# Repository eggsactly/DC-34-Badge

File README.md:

# About
DC-34 Badge contains the KiCad 6 design files for the Cyber Professionals 
Enthusiast Club (CPEC) DEFCON 34 Badge. 

## Board Features
- 2.2" 320x240 display
- Wifi and Bluetooth LE equiped
- 3 Shitty Add On (SAO) 1.69bis ports equiped with I2C
- Gameboy equivalent buttons
- Rumble pack

## Project Structure
The structure of this repo is organized as such:

| Directory               | About                                                   |
|:------------------------|:--------------------------------------------------------|
| DC-34-Badge             | KiCad 6 Design files                                    |
| digikey-kicad-libraries | Symbol libraries and footprints downloaded from digikey |
| kicad-libraries         | git subtree containing expressif design files           |

## Running
To view schematics, please run KiCad 6.0.11 or later. Change directory into 
DC-34-Badge and run
```
kicad DC-34-Badge.kicad_pro
```

Please note: please run kicad from the same directory as the .kicad_pro file 
is stored because the fp-lib-table and sym-lib-table use relative paths 
so that this project is portable between computers.

# Associated Repos
Board firmware is developed in this repo: 
[https://github.com/wildcat86/DC34-Mech-Badge](https://github.com/wildcat86/DC34-Mech-Badge)

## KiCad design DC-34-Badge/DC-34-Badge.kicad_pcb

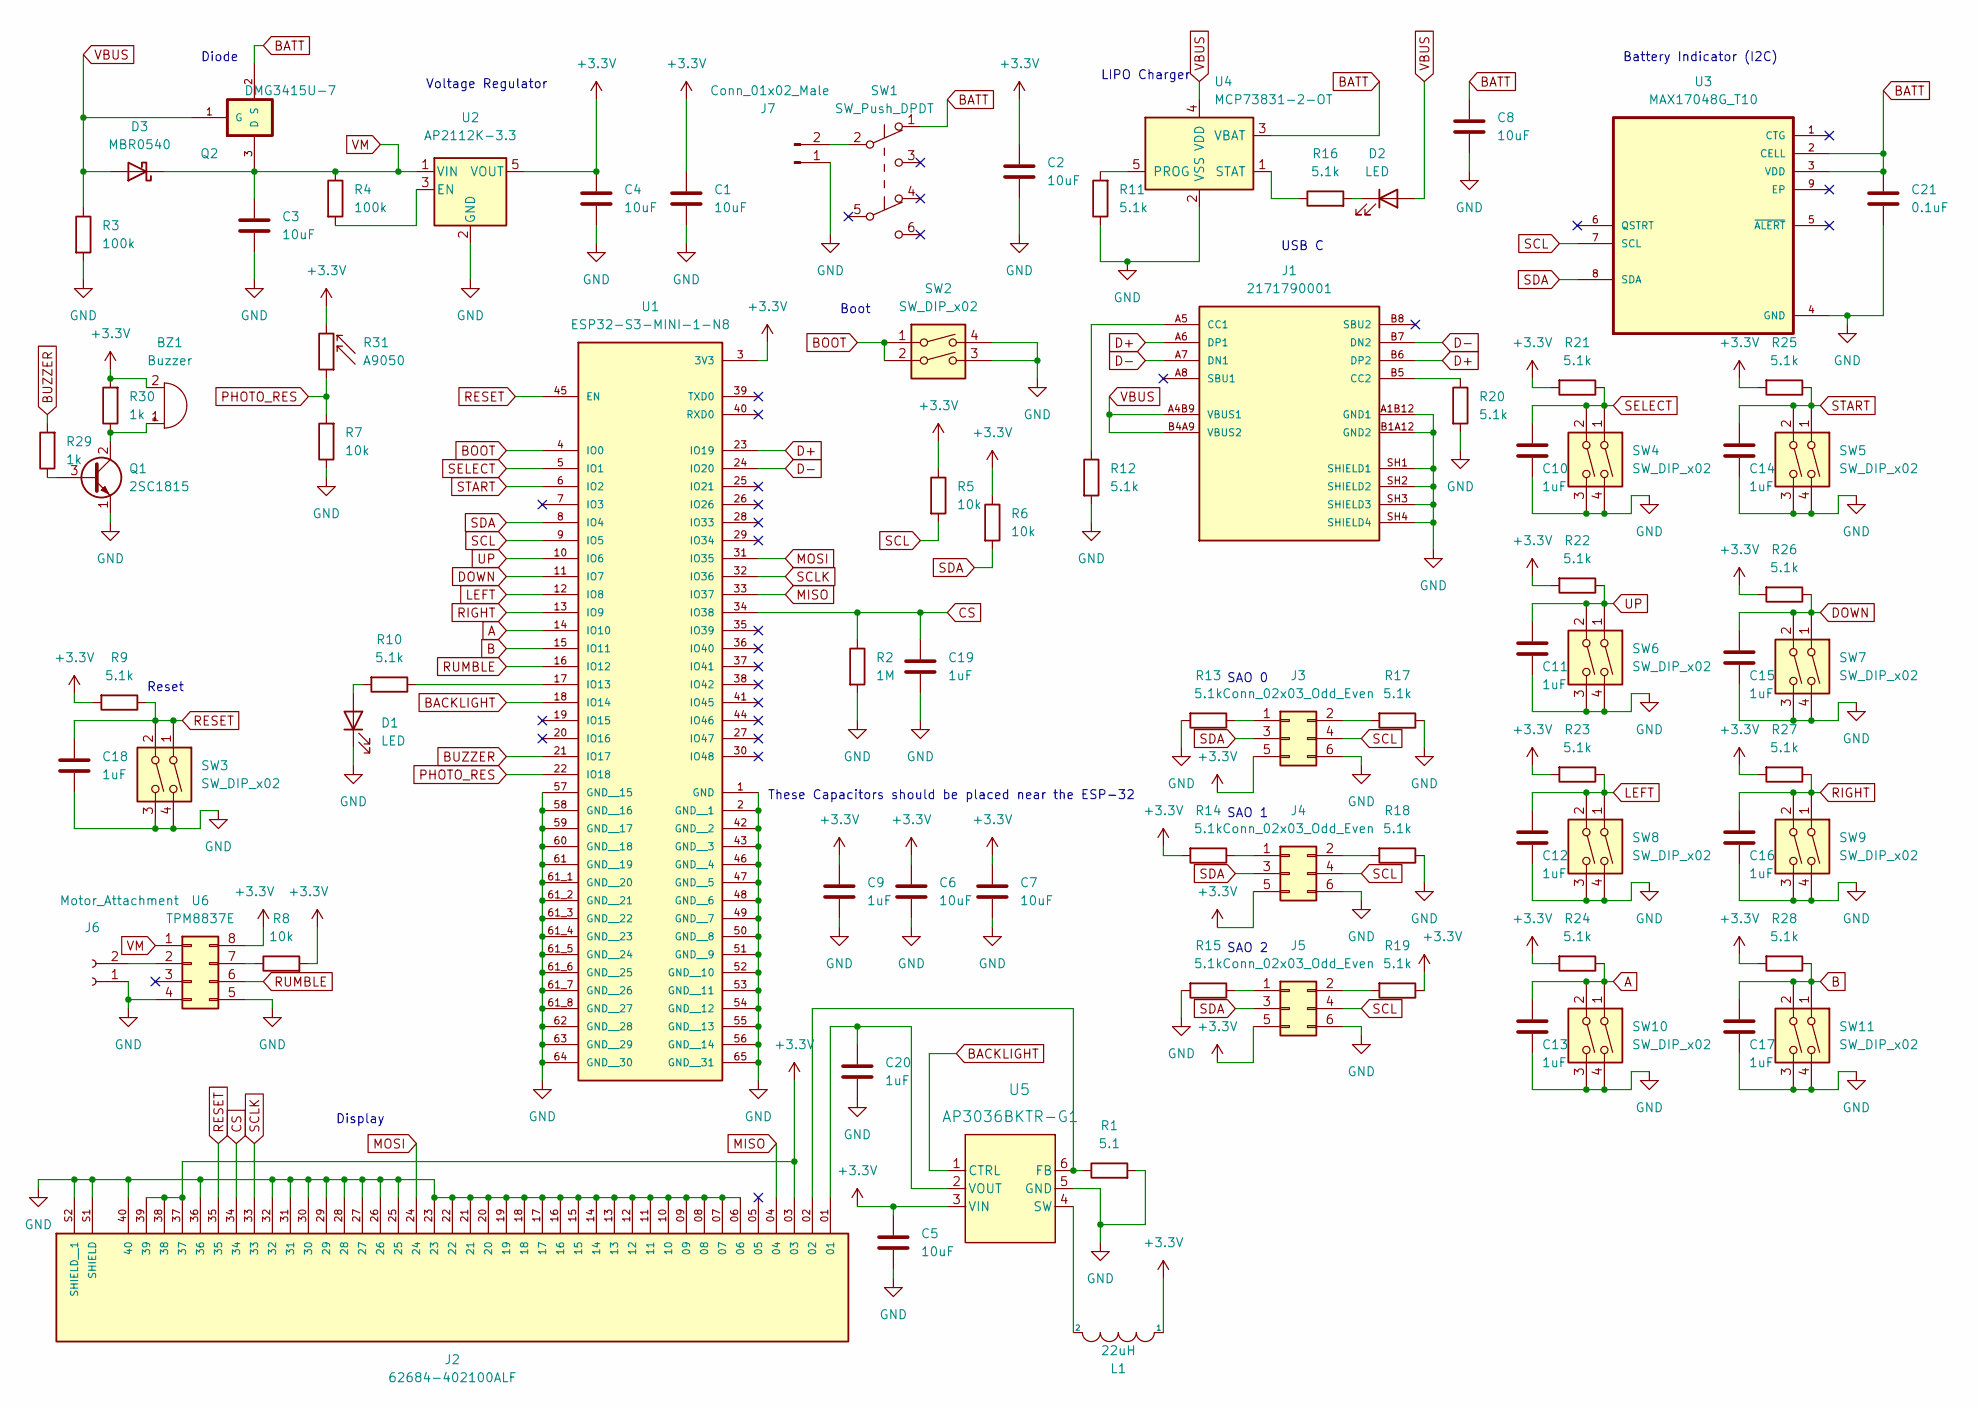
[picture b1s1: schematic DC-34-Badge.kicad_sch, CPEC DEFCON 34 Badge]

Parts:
BZ1: Buzzer; D_A-405_P5.08mm_Vertical_AnodeUp
C1, C2, C3, C4, C5, C6, C7, C8: 10uF; C_0402_1005Metric
C9, C10, C11, C12, C13, C14, C15, C16, C17, C18, C19, C20: 1uF; C_0402_1005Metric
C21: 0.1uF; C_0402_1005Metric
D1, D2: LED; LED_0201_0603Metric
D3: MBR0540; D_SOD-123
J1: 2171790001; MOLEX_2171790001; PARTREV A1
J2: 62684-402100ALF; AMPHENOL_62684-402100ALF; PARTREV AK
J3, J4, J5: Conn_02x03_Odd_Even; PinHeader_2x03_P2.54mm_Vertical
J6: Motor_Attachment; SolderWire-0.1sqmm_1x02_P3.6mm_D0.4mm_OD1mm
J7: Conn_01x02_Male; JST_XH_B2B-XH-AM_1x02_P2.50mm_Vertical
L1: 22uH; L_1210_3225Metric
Q1: 2SC1815; SOT-23
Q2: DMG3415U-7; SOT95P240X105-3N; MPN DMG3415U-7
R1: 5.1; R_0402_1005Metric
R2: 1M; R_0402_1005Metric
R3, R4: 100k; R_0402_1005Metric
R5, R6, R7, R8: 10k; R_0402_1005Metric
R9, R10, R11, R12, R13, R14, R15, R16, R17, R18, R19, R20, R21, R22, R23, R24, R25, R26, R27, R28: 5.1k; R_0402_1005Metric
R29, R30: 1k; R_0402_1005Metric
R31: A9050; R_LDR_5.0x4.1mm_P3mm_Vertical
SW1: SW_Push_DPDT; SW_CuK_JS202011CQN_DPDT_Straight
SW2, SW3, SW4, SW5, SW6, SW7, SW8, SW9, SW10, SW11: SW_DIP_x02; SW_PUSH_6mm
U1: ESP32-S3-MINI-1-N8; XCVR_ESP32-S3-MINI-1-N8; PARTREV v0.6
U2: AP2112K-3.3; SOT-23-5
U3: MAX17048G_T10; SON50P200X200X80-9N
U4: MCP73831-2-OT; SOT-23-5
U5: AP3036BKTR-G1; SOIC6_AP3036BKTR-G1_DIO
U6: TPM8837E; DFN-8-1EP_2x2mm_P0.5mm_EP0.8x1.6mm

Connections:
+3.3V: BZ1.2 (+), C1.1, C2.1, C4.1, C5.1, C6.1, C7.1, C9.1, J2.03, J2.37, J2.38, J2.39, J3.5, J4.5, J5.5, L1.1, R5.1, R6.1, R8.2, R9.2, R14.2, R19.1, R21.2, R22.2, R23.2, R24.2, R25.2, R26.2, R27.2, R28.2, R30.2, R31.2, U1.3 (3V3), U2.5 (VOUT), U5.3 (VIN), U6.8
A: C13.1, R24.1, SW10.1, SW10.2, U1.14 (IO10)
B: C17.1, R28.1, SW11.1, SW11.2, U1.15 (IO11)
BACKLIGHT: U1.18 (IO14), U5.1 (CTRL)
BATT: C8.1, C21.1, Q2.2 (S), SW1.1 (A), U3.2 (CELL), U3.3 (VDD), U4.3 (VBAT)
BOOT: SW2.1, SW2.2, U1.4 (IO0)
BUZZER: R29.2, U1.21 (IO17)
CS: C19.1, J2.34, R2.1, U1.34 (IO38)
D+: J1.A6 (DP1), J1.B6 (DP2), U1.23 (IO19)
D-: J1.A7 (DN1), J1.B7 (DN2), U1.24 (IO20)
DOWN: C15.1, R26.1, SW7.1, SW7.2, U1.11 (IO7)
GND: C1.2, C2.2, C3.2, C4.2, C5.2, C6.2, C7.2, C8.2, C9.2, C10.2, C11.2, C12.2, C13.2, C14.2, C15.2, C16.2, C17.2, C18.2, C19.2, C20.2, C21.2, D1.1 (K), J1.A1B12 (GND1), J1.B1A12 (GND2), J1.SH1 (SHIELD1), J1.SH2 (SHIELD2), J1.SH3 (SHIELD3), J1.SH4 (SHIELD4), J2.06, J2.07, J2.08, J2.09, J2.10, J2.11, J2.12, J2.13, J2.14, J2.15, J2.16, J2.17, J2.18, J2.19, J2.20, J2.21, J2.22, J2.23, J2.25, J2.26, J2.27, J2.28, J2.29, J2.30, J2.31, J2.32, J2.36, J2.40, J2.S1 (SHIELD), J2.S2 (SHIELD__1), J3.6, J4.6, J5.6, J6.1, J7.1, Q1.1 (E), R1.2, R2.2, R3.2, R7.1, R11.1, R12.2, R13.2, R15.2, R17.1, R18.1, R20.2, SW2.3, SW2.4, SW3.3, SW3.4, SW4.3, SW4.4, SW5.3, SW5.4, SW6.3, SW6.4, SW7.3, SW7.4, SW8.3, SW8.4, SW9.3, SW9.4, SW10.3, SW10.4, SW11.3, SW11.4, U1.1 (GND), U1.2 (GND__1), U1.42 (GND__2), U1.43 (GND__3), U1.46 (GND__4), U1.47 (GND__5), U1.48 (GND__6), U1.49 (GND__7), U1.50 (GND__8), U1.51 (GND__9), U1.52 (GND__10), U1.53 (GND__11), U1.54 (GND__12), U1.55 (GND__13), U1.56 (GND__14), U1.57 (GND__15), U1.58 (GND__16), U1.59 (GND__17), U1.60 (GND__18), U1.61 (GND__19), U1.61_1 (GND__20), U1.61_2 (GND__21), U1.61_3 (GND__22), U1.61_4 (GND__23), U1.61_5 (GND__24), U1.61_6 (GND__25), U1.61_7 (GND__26), U1.61_8 (GND__27), U1.62 (GND__28), U1.63 (GND__29), U1.64 (GND__30), U1.65 (GND__31), U2.2 (GND), U3.4 (GND), U4.2 (VSS), U5.5 (GND), U6.4, U6.5
LEFT: C12.1, R23.1, SW8.1, SW8.2, U1.12 (IO8)
MISO: J2.04, U1.33 (IO37)
MOSI: J2.24, U1.31 (IO35)
unnamed: BZ1.1 (-), Q1.2 (C), R30.1
unnamed: C20.1, J2.01, U5.2 (VOUT)
unnamed: D1.2 (A), R10.2
unnamed: D2.1 (K), R16.2
unnamed: J1.A5 (CC1), R12.1
unnamed: J1.B5 (CC2), R20.1
unnamed: J2.02, R1.1, U5.6 (FB)
unnamed: J3.1, R13.1
unnamed: J3.2, R17.2
unnamed: J4.1, R14.1
unnamed: J4.2, R18.2
unnamed: J5.1, R15.1
unnamed: J5.2, R19.2
unnamed: J6.2, U6.2
unnamed: J7.2, SW1.2 (B)
unnamed: L1.2, U5.4 (SW)
unnamed: Q1.3 (B), R29.1
unnamed: R4.2, U2.3 (EN)
unnamed: R8.1, U6.7
unnamed: R10.1, U1.17 (IO13)
unnamed: R11.2, U4.5 (PROG)
unnamed: R16.1, U4.1 (STAT)
PHOTO_RES: R7.2, R31.1, U1.22 (IO18)
RESET: C18.1, J2.35, R9.1, SW3.1, SW3.2, U1.45 (EN)
RIGHT: C16.1, R27.1, SW9.1, SW9.2, U1.13 (IO9)
RUMBLE: U1.16 (IO12), U6.6
SCL: J3.4, J4.4, J5.4, R5.2, U1.9 (IO5), U3.7 (SCL)
SCLK: J2.33, U1.32 (IO36)
SDA: J3.3, J4.3, J5.3, R6.2, U1.8 (IO4), U3.8 (SDA)
SELECT: C10.1, R21.1, SW4.1, SW4.2, U1.5 (IO1)
START: C14.1, R25.1, SW5.1, SW5.2, U1.6 (IO2)
UP: C11.1, R22.1, SW6.1, SW6.2, U1.10 (IO6)
VBUS: D2.2 (A), D3.2 (A), J1.A4B9 (VBUS1), J1.B4A9 (VBUS2), Q2.1 (G), R3.1, U4.4 (VDD)
VM: C3.1, D3.1 (K), Q2.3 (D), R4.1, U2.1 (VIN), U6.1

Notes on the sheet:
Voltage Regulator
Diode
Battery Indicator (I2C)
SAO 2
SAO 1
Display
USB C
Boot
These Capacitors should be placed near the ESP-32
LIPO Charger
SAO 0
Reset

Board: 2 copper layers, 83 parts (2 on the bottom side), 49 nets, no tracks yet.

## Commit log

2026-03-24 Initial commit.
2026-03-25 Implemented Power System
    Implemented power system circuit in schematic.
2026-03-26 Added USB
    USB Bus added to design.
2026-03-27 Completed Power System
    Board design will power up.
2026-03-28 Base Design Complete
    Full duplication of adafruit design.
2026-03-28 Added Schematic Description
    Added title, date and company.
2026-03-28 Added ZIF Connector
    Added ZIF connector symbol and footprint.
2026-03-28 Updated gitignore
    Added _autosave-DC-34-Badge.kicad_sch file to .gitignore file.
2026-03-28 Made paths relative
    Made paths in fp-lib-table and sym-lib-table relative instead of absolute.
2026-03-28 Buttons and Screen Added
    Added buttons and screen and hooked up to design.
2026-03-28 Added Rumble
    Added H-Bridge to enable motor control from ESP-32.
2026-04-02 Added 40-pin ZIF connector.
2026-04-03 Added libraries for diode for display circuit.
2026-04-03 Added display circuit, buzzer circuit, and rearranged componets.
2026-04-03 Added labels for resistors and capacitors.
2026-04-03 Added README file.
2026-04-03 Added to README.md
2026-04-03 Added more to the README.
2026-04-03 April 3 2026 Meeting
    What was worked on in the Friday collaboration meeting.
2026-04-03 Removed autosave file.
2026-04-03 Added No-Connects to Schematic
    Added no-connects to the schematic to address design rule checker findings.
2026-04-03 Updated README.md
    Added 'Running' Subsection to README.
2026-04-04 Fixed date so that it does not cause issues with Windows kicad.
2026-04-04 Revert "Fixed date so that it does not cause issues with Windows kicad."
    This reverts commit c27fbf2cff545e1d774a93f725a7cd52623fee8b.
2026-04-04 Revert "Reverted the KiCad version from 20211014 to 20220914 (#93)"
    This reverts commit 2f3be4bc595e27d61f933b73df66d1e55d531cf2.
2026-04-04 Added digikey ESP-32-MINI symbol and footprint.
2026-04-04 Updates to the MOLEX footprint.
2026-04-04 Added paths to libraries.
2026-04-05 Removed design errors from schematic.
2026-04-05 Updated circuit.
2026-04-10 Added footprint libraries and placed componets.
